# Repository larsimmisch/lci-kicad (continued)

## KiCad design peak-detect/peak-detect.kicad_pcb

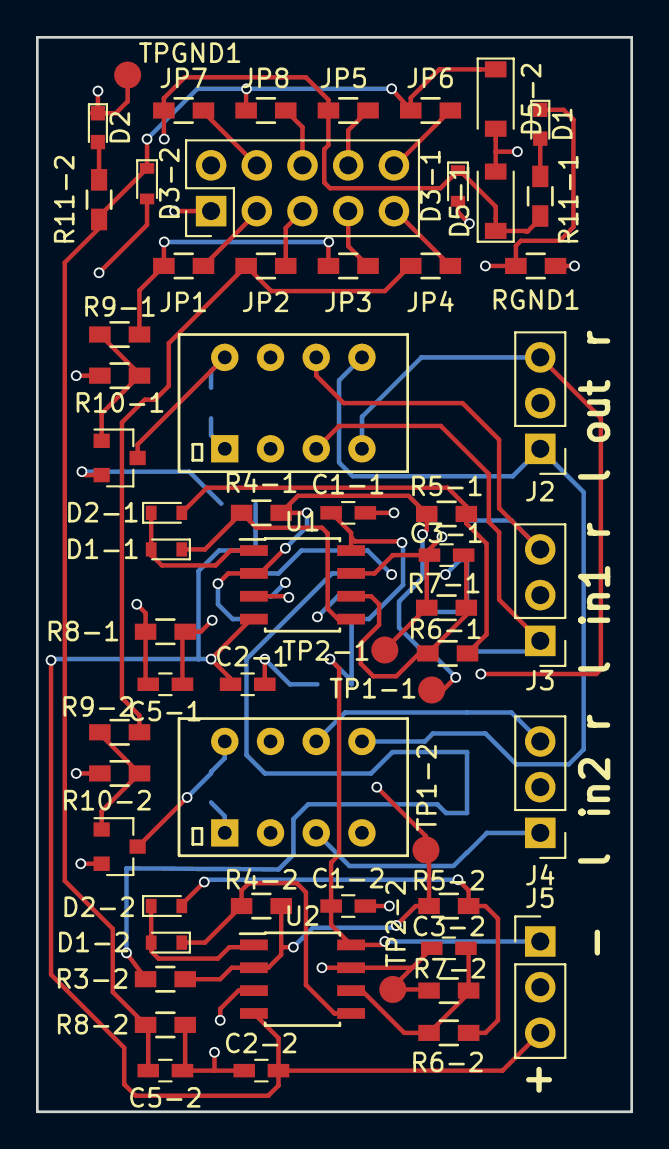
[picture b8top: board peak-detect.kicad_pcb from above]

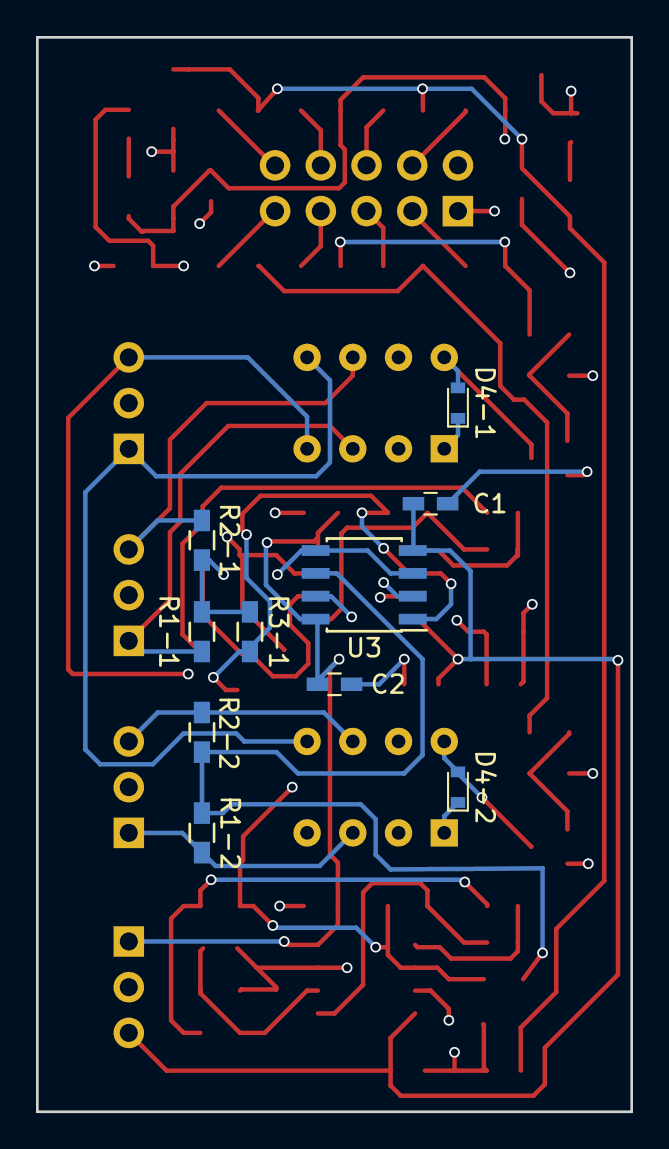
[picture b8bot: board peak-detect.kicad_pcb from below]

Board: 4 copper layers, 33.0 x 59.7 mm, 70 parts (10 on the bottom side), 43 nets.

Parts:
C1, C1-1, C1-2, C2, C2-1, C2-2: 100nF; C_0603_HandSoldering
C3-1, C3-2: 22pF; C_0603_HandSoldering
C5-1, C5-2: 1uF; C_0603_HandSoldering
D1, D2: LED_Small; LED_0603
D1-1, D1-2, D2-1, D2-2, D4-1, D4-2: D; D_0603
D3-1, D3-2: D_Schottky; D_0603
D5-1, D5-2: 3.3V; D_SOD-123
J1: Conn_02x05_Odd_Even; Pin_Header_Straight_2x05_Pitch2.54mm
J2, J3, J4, J5: CONN_01X03; Pin_Header_Straight_1x03_Pitch2.54mm
JP1: Relay-1; R_0603_HandSoldering
JP2: Relay-2; R_0603_HandSoldering
JP3: Relay-3; R_0603_HandSoldering
JP4: Relay-4; R_0603_HandSoldering
JP5: Peak-3; R_0603_HandSoldering
JP6: Peak-4; R_0603_HandSoldering
JP7: Peak-1; R_0603_HandSoldering
JP8: Peak-2; R_0603_HandSoldering
Q1, Q2: BC847; SOT-23
R1-1, R1-2, R2-1, R2-2, R3-1, R3-2, R4-1, R4-2, R5-1, R5-2, R6-1, R6-2, R7-1, R7-2: 10k; R_0603_HandSoldering
R8-1, R8-2, R9-1, R9-2, R10-1, R10-2, R11-1, R11-2: 1k; R_0603_HandSoldering
RGND1: 0; R_0603_HandSoldering
RL1, RL2: Omron_G6K; Omron-G6K
TP1-1, TP1-2, TP2-1, TP2-2: TEST; Measurement_Point_Round-SMD-Pad_Small
TPGND1: TEST; Measurement_Point_Round-SMD-Pad_Small
U1, U2, U3: OPA2134; SOIC-8_3.9x4.9mm_P1.27mm

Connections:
+5V: D4-1.1, D4-2.1, J1.2, RL1.1, RL2.1
GND: J2.2, J3.2, J4.2, RGND1.1, U1.3, U2.3, U3.3, U3.5
GNDD: C1.1, C1-1.1, C1-2.1, C2.1, C2-1.1, C2-2.1, C5-1.1, C5-2.1, D1.1, D2.1, D5-1.2, D5-2.2, J1.1, J5.2, Q1.2, Q2.2, R8-1.1, R8-2.1, R10-1.1, R10-2.1, RGND1.2, TPGND1.1
In-Left-1: J3.1, R1-1.2, RL1.3
In-Left-2: J4.1, R1-2.2, RL2.3
In-Right-1: J3.3, R2-1.2, RL1.6
In-Right-2: J4.3, R2-2.2, RL2.6
unnamed: C3-1.1, D3-1.2, R7-1.1, TP2-1.1, U1.7
unnamed: C3-1.2, R6-1.1, R7-1.2, U1.6
unnamed: C3-2.1, D3-2.2, R7-2.1, TP2-2.1, U2.7
unnamed: C3-2.2, R6-2.1, R7-2.2, U2.6
unnamed: D1-1.1, R4-1.1, U1.5
unnamed: D1-1.2, D2-1.1, U1.1
unnamed: D1-2.1, R4-2.1, U2.5
unnamed: D1-2.2, D2-2.1, U2.1
unnamed: D1.2, R11-1.2
unnamed: D2-1.2, R5-1.1, R6-1.2
unnamed: D2-2.2, R5-2.1, R6-2.2
unnamed: D2.2, R11-2.2
unnamed: D4-1.2, Q1.3, RL1.8
unnamed: D4-2.2, Q2.3, RL2.8
unnamed: J1.3, JP1.2
unnamed: J1.4, JP7.1
unnamed: J1.5, JP2.2
unnamed: J1.6, JP8.1
unnamed: J1.7, JP3.2
unnamed: J1.8, JP5.1
unnamed: J1.9, JP4.2
unnamed: J1.10, JP6.1
unnamed: Q1.1, R9-1.1, R10-1.2
unnamed: Q2.1, R9-2.1, R10-2.2
unnamed: R1-1.1, R2-1.1, R3-1.2, U3.2
unnamed: R1-2.1, R2-2.1, R3-2.2, U3.6
unnamed: R3-1.1, R4-1.2, R5-1.2, TP1-1.1, U1.2, U3.1
unnamed: R3-2.1, R4-2.2, R5-2.2, TP1-2.1, U2.2, U3.7
Out-Left: J2.3, RL1.4, RL2.4
Out-Peak-1: C5-1.2, D3-1.1, D5-1.1, JP5.2, JP7.2, R8-1.2, R11-1.1
Out-Peak-2: C5-2.2, D3-2.1, D5-2.1, JP6.2, JP8.2, R8-2.2, R11-2.1
Out-Right: J2.1, RL1.5, RL2.5
Relay-1: JP1.1, JP3.1, R9-1.2
Relay-2: JP2.1, JP4.1, R9-2.2
U1+: C1-1.2, C1-2.2, C2.2, J5.1, U1.8, U2.8, U3.8
U1-: C1.2, C2-1.2, C2-2.2, J5.3, U1.4, U2.4, U3.4

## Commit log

2015-06-04 Add USb switch
2015-06-04 Add Omron relay
2015-06-04 Stray wire removed
2016-04-13 Lib, docs and a start
2016-04-15 Oops. Accidentally deleted the class-d sheet
2016-05-05 Format, gain, fault & mute LED
2016-05-06 PVDD decoupling and output filters
2016-05-06 Make it a bit prettier
2016-05-14 Schematics for power supplies from webench
    Library reorganisation
2016-05-17 Part numbers
2016-08-09 Add input schematic around DIR9001 (WIP)
2016-08-23 More input
2017-02-20 Add unbalance
2017-02-20 Consistent quadratic soldermask is plus
2017-02-20 Datasheets
2017-05-16 Add peak_detect
2017-09-15 Added virtual ground mixer.
    Back wiring and front placement.
2017-09-19 Add rotary encoder breakout board
2018-02-14 Peak detect routed
2018-02-14 Drill holes, silk screen cleanup
2018-02-14 Back silk screen cleanup.
2018-02-14 Add hifiberry-adc-dac
2018-03-27 Updated to Kicad 5
2018-03-27 Combine libraries
2018-03-27 Update remaining projects to KiCad 5
2018-04-02 LM358 is single supply. Doh.
2018-04-02 SOD-123 footprint for Zener diodes
2018-04-04 Fiddle with the ADC
2019-01-16 Unbalance: grounding scheme is idiotic. peak-detect: forgot what was changed
2019-02-01 Clean up symbols after update/library change
2019-02-11 Add power supply and connector
2019-02-11 Generated gerbers
2019-02-15 Fix footprints
2019-03-13 Fix wrong fottprints (the expensive way)
2019-04-10 Fix Footprint for Reichelt relay
2019-05-08 New power connector and changes trickling out. Redid P2 in Kicad
2019-05-08 Run DRC un P2
2019-05-08 Make garduino a Pi hat
2019-05-10 Schematic and PCB for Pluto mute circuit
2019-05-16 Add humidity sensor
2019-05-16 peak-detect: add mixers humidity-sensor: fix bugs, smaller PCB
2019-05-16 Give peak-detect a mute option
2019-05-17 garduino WIP
2019-05-17 Add P3
2019-05-17 Smaller is better, also fix MISO and sensing (hopefully)
2019-05-17 Route P3 PCB
2019-05-28 Add capsensor, humidity sensor p3, garduino with avr
2019-06-19 Add water-switches
2019-06-21 Add relay to water-switches
2019-07-01 Add SMD version of phonoclone
2019-09-08 Correct footprints
2019-10-16 Add mixer for Tilman.
2019-10-16 Initial placing
2019-10-16 Better placement
2019-10-16 Routed
2019-10-17 Use consistent GNDA pin
2019-10-17 Dual bypass capacitors
2019-10-17 Silkscreen
2019-10-17 More silkscreen
2020-06-10 Garduino with FETs
2020-06-10 Add FTR Lycz relay and RACOM power supply.
2020-08-12 Remove hifiberry-adc-dac, garduino untested
2020-08-21 Route mute, mostly automatic changes for peak-detect
2020-09-13 Safer values, less power consumption
2020-11-18 Better footprints after another simulation run.
2021-01-03 Add espsense
2021-01-04 Add headphone-power
2021-01-04 Fix espsense (phew)
2021-01-04 Sigh
2021-01-04 Sigh2.
2021-01-18 Fix schematic
2021-01-18 Better footprints and fixed pcb
2021-01-18 Rev 2. Sigh.
2023-07-18 Add P4
2023-07-18 Remove template
2023-07-19 Add connections for rotary encoder, display and power relay
2023-07-20 Add transistors for relays
2023-07-29 Add submodule (should not be needed, but is nice as a reference nonetheless)
2024-06-30 Guarduino switched to MCP3008, PCB not done
2024-06-30 Add new files
2024-06-30 gitignore
2024-06-30 Cleanups, placement might work
2024-06-30 Routing done (not pretty)
2024-06-30 Add capacitors for 3.3v
2024-07-01 Add label
2024-07-01 Rename garduino to waterpi
2024-07-01 Add connector for display
2024-07-01 GND connections/warnings
2024-07-01 gerbers are in meta now
2024-07-04 Remove old schematic
2024-07-20 Use SOT-223
2024-07-20 Updates for Kicad 8, different output wiring
2026-02-27 Add Musical Fidelity A1X better preamp board
